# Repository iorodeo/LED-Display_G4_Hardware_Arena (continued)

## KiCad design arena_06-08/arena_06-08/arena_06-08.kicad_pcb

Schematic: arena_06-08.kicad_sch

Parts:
C1: 0.1µF; CP_Radial_Tantal_D4.5mm_P2.50mm; Digi-Key 478-9315-ND
C2, C3, C5, C6: 0.1µF; CP_Radial_Tantal_D4.5mm_P2.50mm
C4: 47µF; CP_Radial_Tantal_D4.5mm_P2.50mm
H1, H2, H3, H4: MountingHole_Pad; MountingHole_4.5mm_Pad_Via
J1: Col1a; PinSocket_1x15_P2.54mm_Vertical; DigiKey PPPC151LFBN-RC
J2: Col2a; PinSocket_1x15_P2.54mm_Vertical
J3: Col1b; PinSocket_1x15_P2.54mm_Vertical
J4: Col2b; PinSocket_1x15_P2.54mm_Vertical
J5: Col3a; PinSocket_1x15_P2.54mm_Vertical
J6: Col4a; PinSocket_1x15_P2.54mm_Vertical
J7: Col3b; PinSocket_1x15_P2.54mm_Vertical
J8: Col4b; PinSocket_1x15_P2.54mm_Vertical
J9: Barrel_Jack; BarrelJack_Kycon_KLDX-0202-xC_Horizontal
J10, J11: RJ45_Amphenol_RJMG1BD3B8K1ANR
R1, R2, R3, R4, R5, R6, R7, R8, R9, R10, R11, R12: 10k; R_Axial_DIN0204_L3.6mm_D1.6mm_P1.90mm_Vertical
U1, U2: Teensy4.1; Teensy41

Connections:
+5V: C1.2, C2.1, C3.1, C4.1, J1.1, J2.1, J3.1, J4.1, J5.1, J6.1, J7.1, J8.1, J9.1, R1.1, R2.1, R3.1, R4.1, R5.1, R6.1, R7.1, R8.1, R9.1, R10.1, R11.1, R12.1, U1.48 (VIN), U2.48 (VIN)
/CS1_1: J1.7, U1.12 (10_CS_MQSR)
/CS1_2: J1.8, U1.11 (9_OUT1C)
/CS1_3: J3.9, U1.10 (8_TX2_IN1)
/CS1_4: J3.10, U1.9 (7_RX2_OUT1A)
/CS2_1: J2.7, U1.30 (38_CS1_IN1)
/CS2_2: J2.8, U1.29 (37_CS)
/CS2_3: J4.9, U1.28 (36_CS)
/CS2_4: J4.10, U1.27 (35_TX8)
/CS3_1: J5.7, U2.12 (10_CS_MQSR)
/CS3_2: J5.8, U2.11 (9_OUT1C)
/CS3_3: J7.9, U2.10 (8_TX2_IN1)
/CS3_4: J7.10, U2.9 (7_RX2_OUT1A)
/CS4_1: J6.7, U2.30 (38_CS1_IN1)
/CS4_2: J6.8, U2.29 (37_CS)
/CS4_3: J8.9, U2.28 (36_CS)
/CS4_4: J8.10, U2.27 (35_TX8)
/SCK1: J1.4, J3.4, U1.35 (13_SCK_LED)
/SCK2: J2.4, J4.4, U1.19 (27_A13_SCK1)
/SCK3: J5.4, J7.4, U2.35 (13_SCK_LED)
/SCK4: J6.4, J8.4, U2.19 (27_A13_SCK1)
/SDO1: J1.5, J3.5, U1.13 (11_MOSI_CTX1)
/SDO2: J2.5, J4.5, U1.18 (26_A12_MOSI1)
/SDO3: J5.5, J7.5, U2.13 (11_MOSI_CTX1)
/SDO4: J6.5, J8.5, U2.18 (26_A12_MOSI1)
/T1L: J10.L4 (LEDG_A), U1.61 (LED)
/T1R+: J10.R3 (RD+), U1.60 (R+)
/T1R-: J10.R6 (RD-), U1.65 (R-)
/T1T+: J10.R1 (TD+), U1.63 (T+)
/T1T-: J10.R2 (TD-), U1.62 (T-)
/T2L: J11.L4 (LEDG_A), U2.61 (LED)
/T2R+: J11.R3 (RD+), U2.60 (R+)
/T2R-: J11.R6 (RD-), U2.65 (R-)
/T2T+: J11.R1 (TD+), U2.63 (T+)
/T2T-: J11.R2 (TD-), U2.62 (T-)
GND: C1.1, C2.2, C3.2, C4.2, C5.2, C6.2, H1.1, H2.1, H3.1, H4.1, J1.2, J2.2, J3.2, J4.2, J5.2, J6.2, J7.2, J8.2, J9.2, J9.3, J10.L3 (LEDG_K), J10.R8 (GND), J11.L3 (LEDG_K), J11.R8 (GND), U1.47 (GND), U1.64 (GND), U2.47 (GND), U2.64 (GND)
unnamed: C5.1, J11.R4 (TCT), J11.R5 (RCT)
unnamed: C6.1, J10.R4 (TCT), J10.R5 (RCT)
unnamed: J1.9, J1.10, J1.11, J1.12, J1.13, R1.2
unnamed: J2.9, J2.10, J2.11, J2.12, J2.13, R2.2
unnamed: J3.7, J3.8, R4.2
unnamed: J3.11, J3.12, J3.13, R3.2
unnamed: J4.7, J4.8, R6.2
unnamed: J4.11, J4.12, J4.13, R5.2
unnamed: J5.9, J5.10, J5.11, J5.12, J5.13, R7.2
unnamed: J6.9, J6.10, J6.11, J6.12, J6.13, R8.2
unnamed: J7.7, J7.8, R10.2
unnamed: J7.11, J7.12, J7.13, R9.2
unnamed: J8.7, J8.8, R12.2
unnamed: J8.11, J8.12, J8.13, R11.2

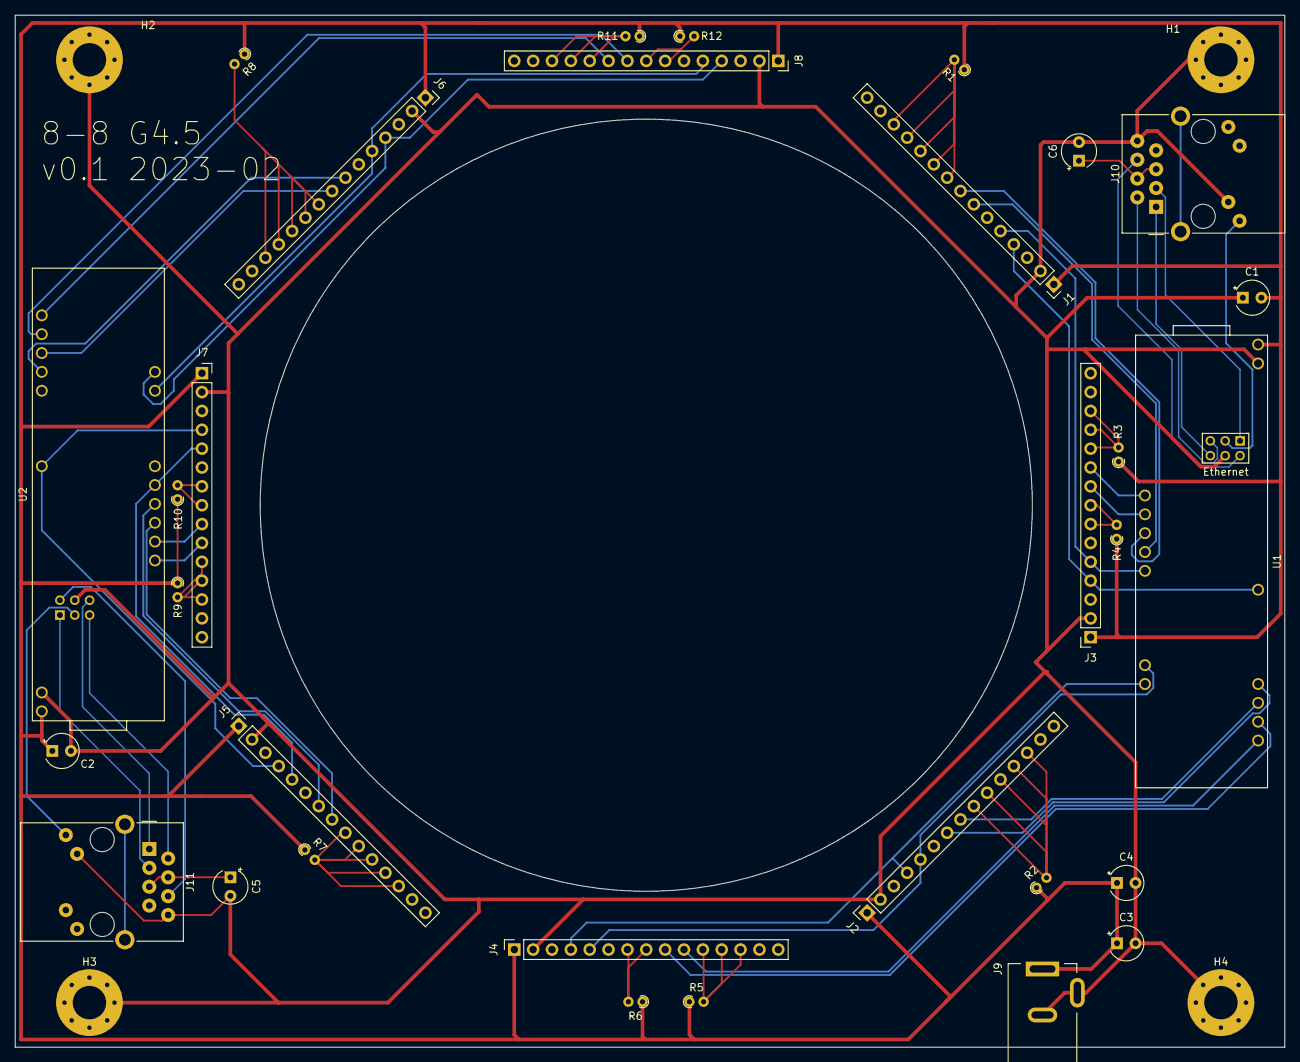
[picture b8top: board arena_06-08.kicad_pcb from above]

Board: 2 copper layers, 171.0 x 139.0 mm, 35 parts (0 on the bottom side), 50 nets.

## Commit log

2023-08-03 update top acrylic 11-18
2024-10-08 update reference to latest design, fix BOM
2024-10-08 initial design for 06-08 arena, 2x teensy 4.1
2024-10-08 add mask layer to gerbers
2024-10-08 cleanup
2024-10-08 double checking, adding BOM
2024-10-09 ready order ni and teensy 12-12, cleanup development
2024-10-09 more cleanup, more explanation
2024-10-09 config already in assets, remove tmp files
2024-10-09 remove misleading BOM
2024-10-09 cleanup teensy arena v0p2
2024-10-09 remove backups from git
2024-10-09 cleanup arena 06 production files
2024-10-09 flatten path structure
2024-10-09 update documentation
2024-12-02 Worked on 12-12 teensy4p1 arena without vreg.
    Modified SPI connections from teensy to panel columns so that all
    signals go from a single source to a single destinatin. Also, added
    source termination resistors and schmitt trigger buffers to all SPI
    signals.
2024-12-02 More work on schematic for 12-12 teensy arena.
2024-12-03 More work on schematic.
2024-12-03 Reworked schematic for 12-12 teensy arena w/o regulators some more.
    Worked on foot print assignmets. Started replacing some of the single
    schmitt triggers with equivalent dual versions to reduce component
    count.
2024-12-05 Finished initial schematic for 12-12 teensy 4.1 arena w/o vreg.
    Finished footprint assignments and started working on layout changes.
2024-12-05 Added source termination resistors to miso lines.
2024-12-11 Worked on 12-12 arena layout.
2024-12-11 Removed .swp file.
2024-12-12 Finished preliminary layout for new 12-12 teensy 4.1 arena.
    Includes source termination resistors and schmitt trigger buffers.
2024-12-13 Added for 12-12 arena top.
2024-12-19 Worked on prelimnary hand routing of 12-12 teensy 4.1 arena.
2024-12-19 Finished hand route of 12-12 teensy arena. Finished route of 12-12 top.
2024-12-19 Added sprectra .ses file for first complete route - not fully optimized.
2024-12-20 Added refined spectra session file for 12-12 teensy arena.
2024-12-20 Completed routing of 12-12 teensy 4.1 arena.
2024-12-20 Finished initial verions of fab files for 12-12 teensy 4.1 arena. Need to check orientations.
2024-12-20 Minor changes for fab file creation.
2024-12-20 Fixed orientations in 12-12 teensy 4.1 arena fab files.
2024-12-20 Added fab files for 12-12 arena top.
